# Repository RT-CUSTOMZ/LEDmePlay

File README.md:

# LEDmeplay-ESP32: Retro Arcade auf dem 32x32 RGB-Matrix-Display

Willkommen zum LEDmeplay-ESP32-Projekt!  

Dieses Projekt bringt die klassischen LEDmeplay-Spiele von Mithotronic auf ein neues Level: Mit einem leistungsstarken ESP32 als Herzstück lassen sich mehrere Arcade-Spiele auf einem 32x32 Punkte großen RGB-LED-Matrix-Display ausführen und bequem über ein Startmenü auswählen.  
Ziel ist es, ein modulares Open-Source-System zu bieten, das an das Ursprungsprojekt **LEDmeplay für Arduino Mega 2560** anknüpft, aber durch die neue Hardware umfangreicher, moderner und vielseitiger wird.

## Übersicht

- **Plattform:** ESP32
- **Display:** 32x32 RGB-Matrix-LEDs
- **Projekttyp:** PlattformIO-Projekt (Arduino-Shell)
- **Basis:** Erweiterung des Originals von Mithotronic
- **Weitere Inhalte:** FreeCAD-Dateien (Gehäuse-Design als 3D-Druck), KiCad-Schaltpläne (Elektronik), SVG (Laser-Dateien für Gehäuse)

## Hauptfeatures & Verbesserungen

- **Mehrere Spiele:** Dank ESP32 können viele Spiele im Flash gespeichert und via Startmenü ausgewählt werden.
- **Zentrale Spiele-Bibliothek:** Gemeinsame Spiel-Logik und wiederkehrende Routinen wurden als Bibliothek gekapselt – optimale Basis für eigene Spiele-Entwicklungen und unkomplizierte Erweiterbarkeit.
- **Konstante Spielgeschwindigkeit:** Trotz höherer CPU-Geschwindigkeit laufen die klassischen Spiele weiterhin in Original-Geschwindigkeit.
- **Möglichkeit für aufwendigere Spiele:** Der ESP32 eröffnet neue Potenziale für anspruchsvollere Spiele.
- **Gut dokumentierte Beispieldateien:** CAD- und Layout-Daten unterstützen beim Nachbau.

## Bekannte Einschränkungen

- **IO-Pin-Engpass:** Die verfügbaren Pins des ESP32 sind durch Display, Steuerelemente u.a. Geräte fast vollständig belegt.
- **Gestiegene Komplexität:** Das Management mehrerer Spiele sowie die Menüstrukturen erhöhen die Komplexität des Codes. Dies kann das ursprüngliche Ziel, Einsteigerinnen und Einsteigern das Programmieren beizubringen, erschweren.

## Projektstruktur

Das Repository ist logisch gegliedert – jedes Unterverzeichnis enthält klar umrissene Inhalte für die einzelnen Projektaspekte:

| Verzeichnis         | Inhalt                                                                                  |
|---------------------|----------------------------------------------------------------------------------------|
| `/src`              | Hauptquellcode für das ESP32-Board, inkl. Spiele, Menü, Bibliotheken                   |
| `/lib`              | Wiederverwendbare Bibliotheken für Spiel-Logik, Displaysteuerung usw.                  |
| `/data`             | Ressourcen wie Fonts, Sprites und Leveldaten                                           |
| `/hardware/` | FreeCAD-Dateien für alle Gehäuseteile (STL für 3D-Druck lassen sich daraus erzeugen) sowie SVG-Dateien, um Gehäuseteile (Frontplatte, Halterungen) mit dem Lasercutter zu fertigen  |
| `/hardware/KiCad/`   | KiCad-Projektdateien, Schaltpläne und Boardlayouts für die Elektronik                  |
| `/docs`             | Dokumentation, Tutorials, Installationsanleitungen                                     |

## Installation & Quickstart

1. **Voraussetzungen**
    - ESP32-Board
    - Windows, Mac oder Linux mit [PlatformIO](https://platformio.org/) und Arduino-Core
    - Lötkolben und Basiselektronik-Kenntnisse für Aufbau

2. **Firmware flashen**
    - Repository klonen:
      ```bash
      git clone https://github.com/RT-CUSTOMZ/LEDmePlay.git
      ```
    - PlatformIO-Projekt in VSCode öffnen
    - Board- und Port-Einstellungen anpassen (siehe `platformio.ini`)
    - Kompilieren & Upload:
      ```bash
      pio run --target upload
      ```

3. **Spiele auswählen**
    - Das Startmenü erscheint automatisch nach dem Boot.
    - Spiele lassen sich über angeschlossene Taster auswählen und starten.

## Hardware & Gehäuse

- **3D-Druckteile:**  
  Im Verzeichnis `/hardware/freecad` findest du alle FreeCAD-Dateien (FCStd), mit denen du die Gehäuseteile (z.B. Frontplatten, Halterungen) direkt im 3D-Drucker als STL exportieren kannst.

- **Elektronik und Platinen:**  
  Die Schaltpläne und Board-Layouts sind im Verzeichnis `/hardware/kicad` als KiCad-Projekt (Schaltplandateien, PCB) abgelegt.

- **Laser-Dateien:**  
  Vorlagen für Lasercutter (z.B. Acryl-Front, Tasten-Bohrungen) befinden sich unter `/hardware/`.

## Eigene Spiele entwickeln

- Die gemeinsame Spielelogik steht als Bibliothek unter `/lib` zur Verfügung.
- Beispielprojekte im `/src`-Verzeichnis können dupliziert und angepasst werden.

## Hinweise & Credits

- Dieses Projekt basiert auf dem genialen Ansatz von [Mithotronic LEDmeplay](https://mithotronic.de/ledmeplay.php)
- Bitte respektiere Lizenzen und Quellen beim Weiterverbreiten und Forken.
- Feedback, Fehlerberichte und Spielbeiträge gerne als Pull Request!

**Viel Spaß mit LEDmeplay-ESP32!**

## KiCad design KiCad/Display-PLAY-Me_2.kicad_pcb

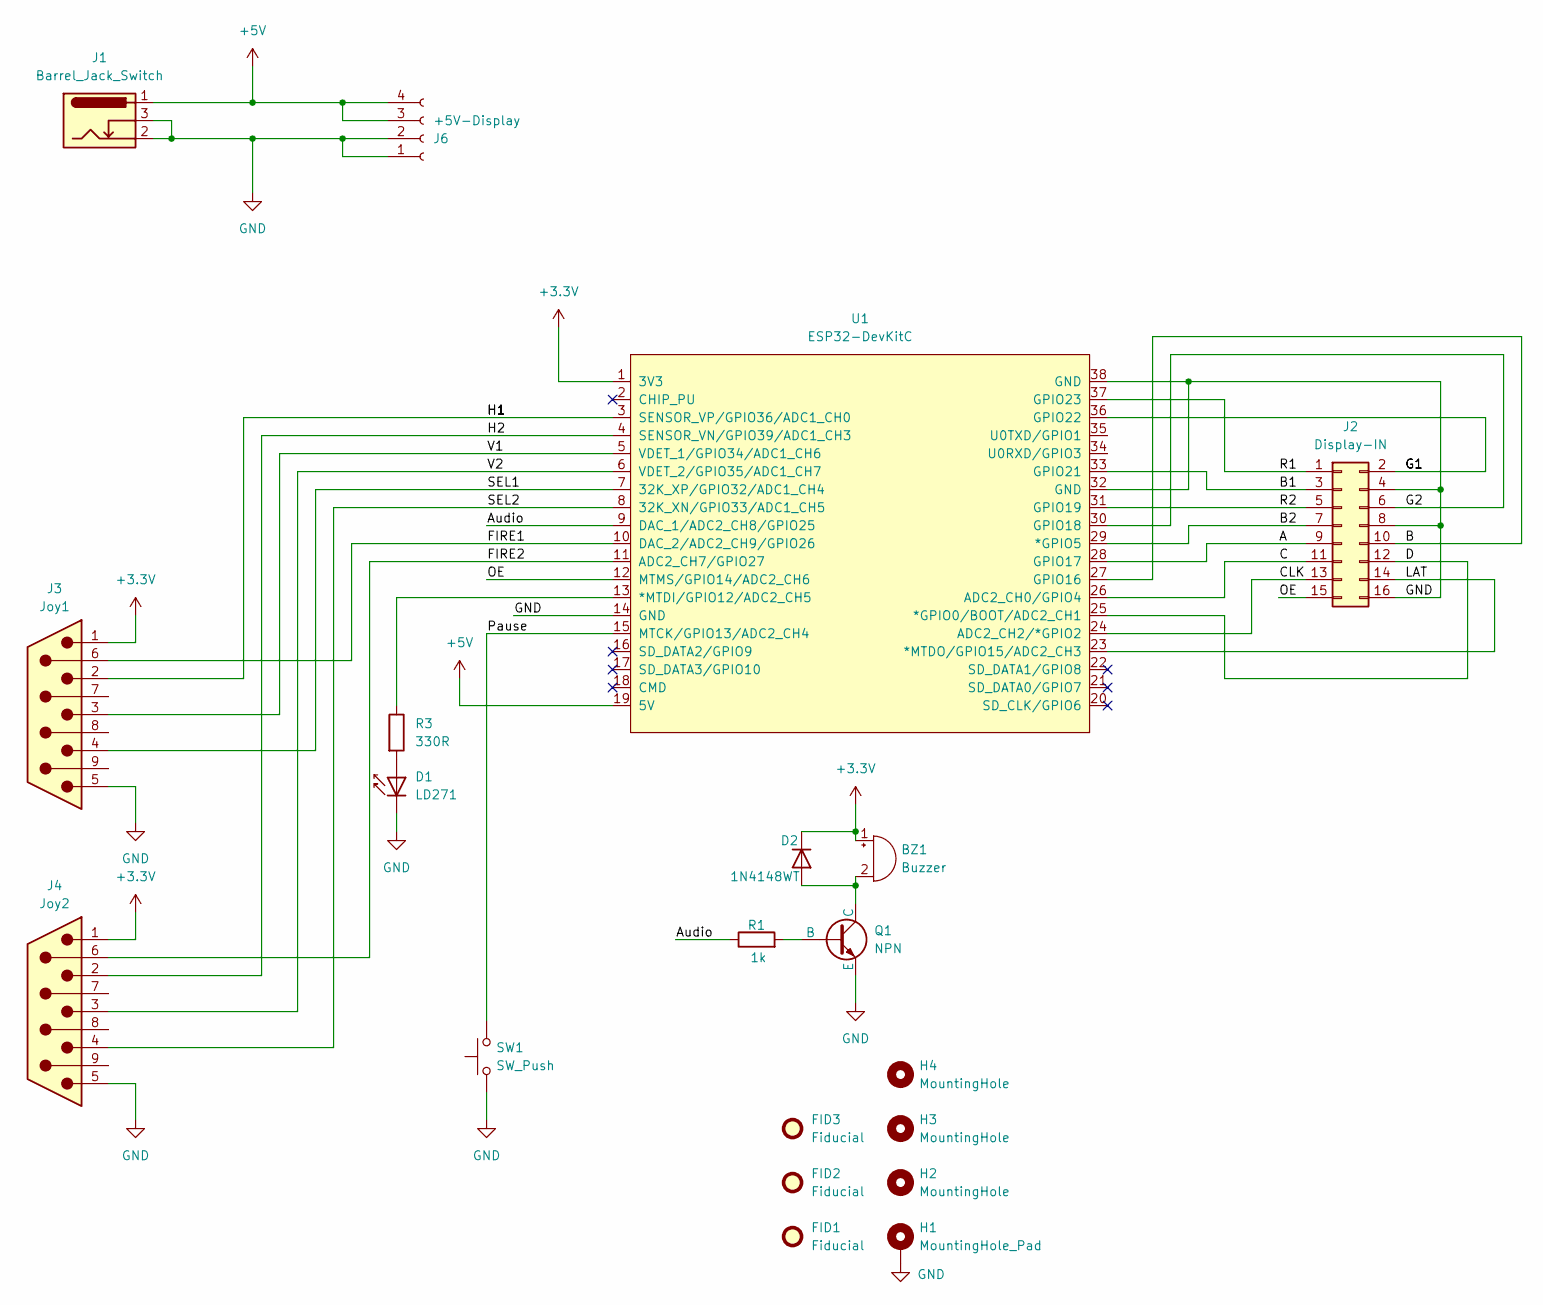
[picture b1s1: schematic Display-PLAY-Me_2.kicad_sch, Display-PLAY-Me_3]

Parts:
BZ1: Buzzer; MagneticBuzzer_PUI_AT-0927-TT-6-R
D1: LD271; LED_D5.0mm_IRGrey
D2: 1N4148WT; D_A-405_P12.70mm_Horizontal
FID1, FID2, FID3: Fiducial; Fiducial_1.5mm_Mask3mm
H1: MountingHole_Pad; MountingHole_3.5mm_Pad_TopBottom
H2, H3, H4: MountingHole; MountingHole_3.5mm
J1: Barrel_Jack_Switch; BarrelJack_Wuerth_6941xx301002
J2: Display-IN; IDC-Header_2x08_P2.54mm_Vertical
J3: Joy1; DSUB-9_Female_Horizontal_P2.77x2.84mm_EdgePinOffset4.94mm_H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
J4: Joy2; DSUB-9_Female_Horizontal_P2.77x2.84mm_EdgePinOffset4.94mm_H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
J6: +5V-Display; PhoenixContact_MSTBA_2,5_4-G-5,08_1x04_P5.08mm_Horizontal
Q1: NPN; TO-92L
R1: 1k; R_Axial_DIN0207_L6.3mm_D2.5mm_P10.16mm_Horizontal
R3: 330R; R_Axial_DIN0207_L6.3mm_D2.5mm_P10.16mm_Horizontal
SW1: SW_Push; SW_Tactile_SPST_Angled_PTS645Vx31-2LFS
U1: ESP32-DevKitC

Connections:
+3.3V: BZ1.1 (+), D2.1 (K), J3.1, J4.1, U1.1 (3V3)
+5V: J1.1, J6.3, J6.4, U1.19 (5V)
/A: J2.9, U1.28 (GPIO17)
/Audio: R1.1, U1.9 (DAC_1/ADC2_CH8/GPIO25)
/B: J2.10, U1.27 (GPIO16)
/B1: J2.3, U1.33 (GPIO21)
/B2: J2.7, U1.29 (*GPIO5)
/C: J2.11, U1.26 (ADC2_CH0/GPIO4)
/CLK: J2.13, U1.24 (ADC2_CH2/*GPIO2)
/D: J2.12, U1.25 (*GPIO0/BOOT/ADC2_CH1)
/FIRE1: J3.6, U1.10 (DAC_2/ADC2_CH9/GPIO26)
/FIRE2: J4.6, U1.11 (ADC2_CH7/GPIO27)
/G2: J2.6, U1.30 (GPIO18)
/H2: J4.2, U1.4 (SENSOR_VN/GPIO39/ADC1_CH3)
/LAT: J2.14, U1.23 (*MTDO/GPIO15/ADC2_CH3)
/OE: J2.15, U1.12 (MTMS/GPIO14/ADC2_CH6)
/Pause: SW1.2, U1.15 (MTCK/GPIO13/ADC2_CH4)
/R1: J2.1, U1.37 (GPIO23)
/R2: J2.5, U1.31 (GPIO19)
/SEL1: J3.4, U1.7 (32K_XP/GPIO32/ADC1_CH4)
/SEL2: J4.4, U1.8 (32K_XN/GPIO33/ADC1_CH5)
/V1: J3.3, U1.5 (VDET_1/GPIO34/ADC1_CH6)
/V2: J4.3, U1.6 (VDET_2/GPIO35/ADC1_CH7)
GND: D1.1 (K), H1.1, J1.2, J1.3, J2.4, J2.8, J2.16, J3.5, J4.5, J6.1, J6.2, Q1.3 (E), SW1.1, U1.14 (GND), U1.32 (GND), U1.38 (GND)
unnamed: BZ1.2 (-), D2.2 (A), Q1.1 (C)
unnamed: D1.2 (A), R3.2
unnamed: J2.2, U1.36 (GPIO22)
unnamed: Q1.2 (B), R1.2
unnamed: R3.1, U1.13 (*MTDI/GPIO12/ADC2_CH5)
unnamed: J3.2, U1.3 (SENSOR_VP/GPIO36/ADC1_CH0)

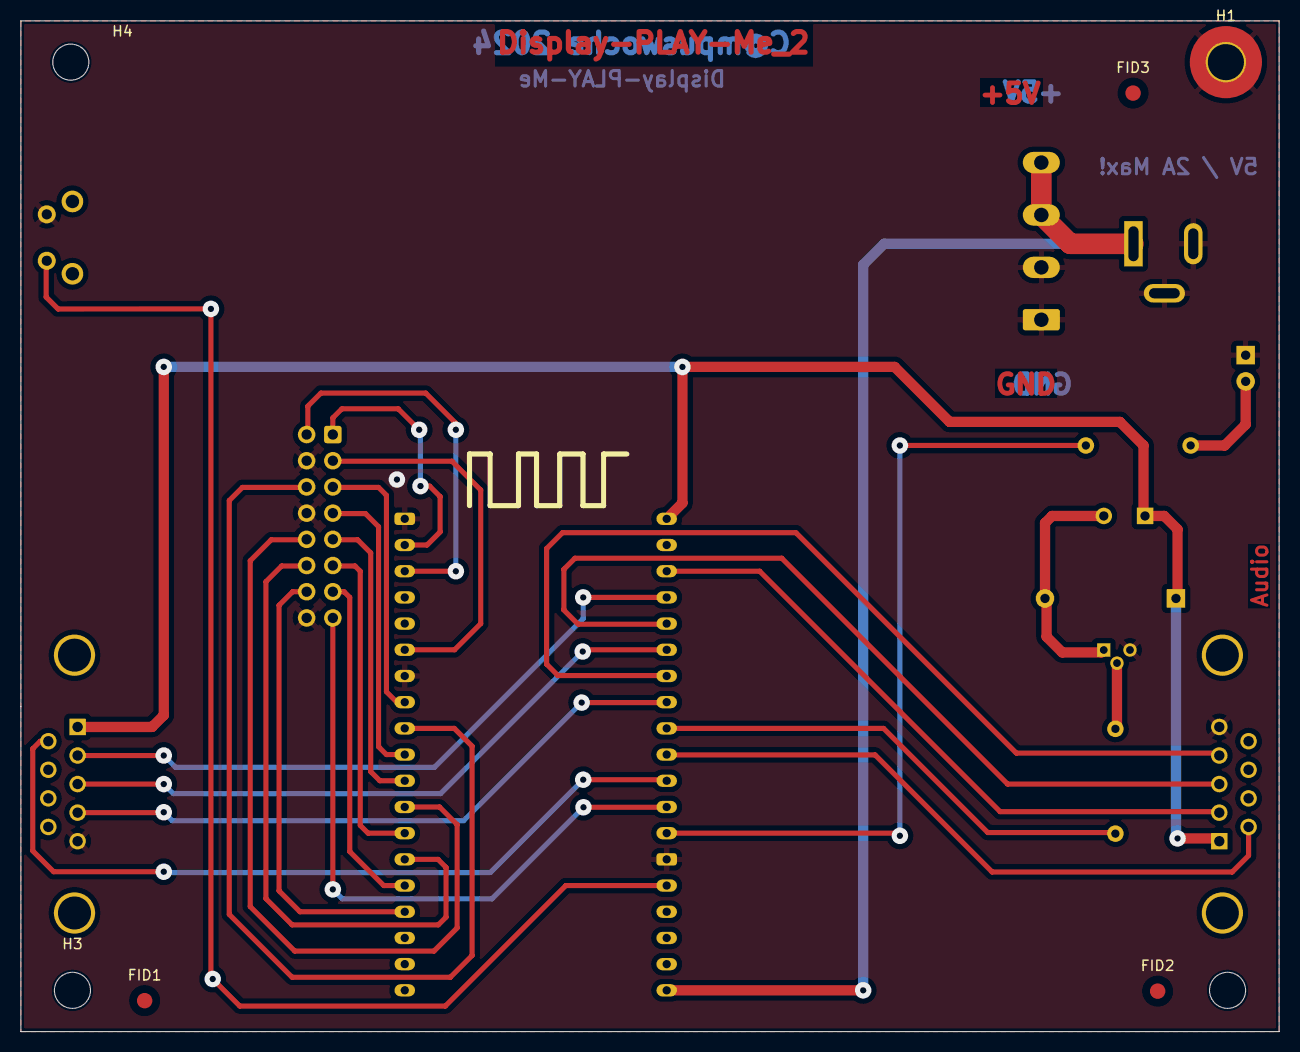
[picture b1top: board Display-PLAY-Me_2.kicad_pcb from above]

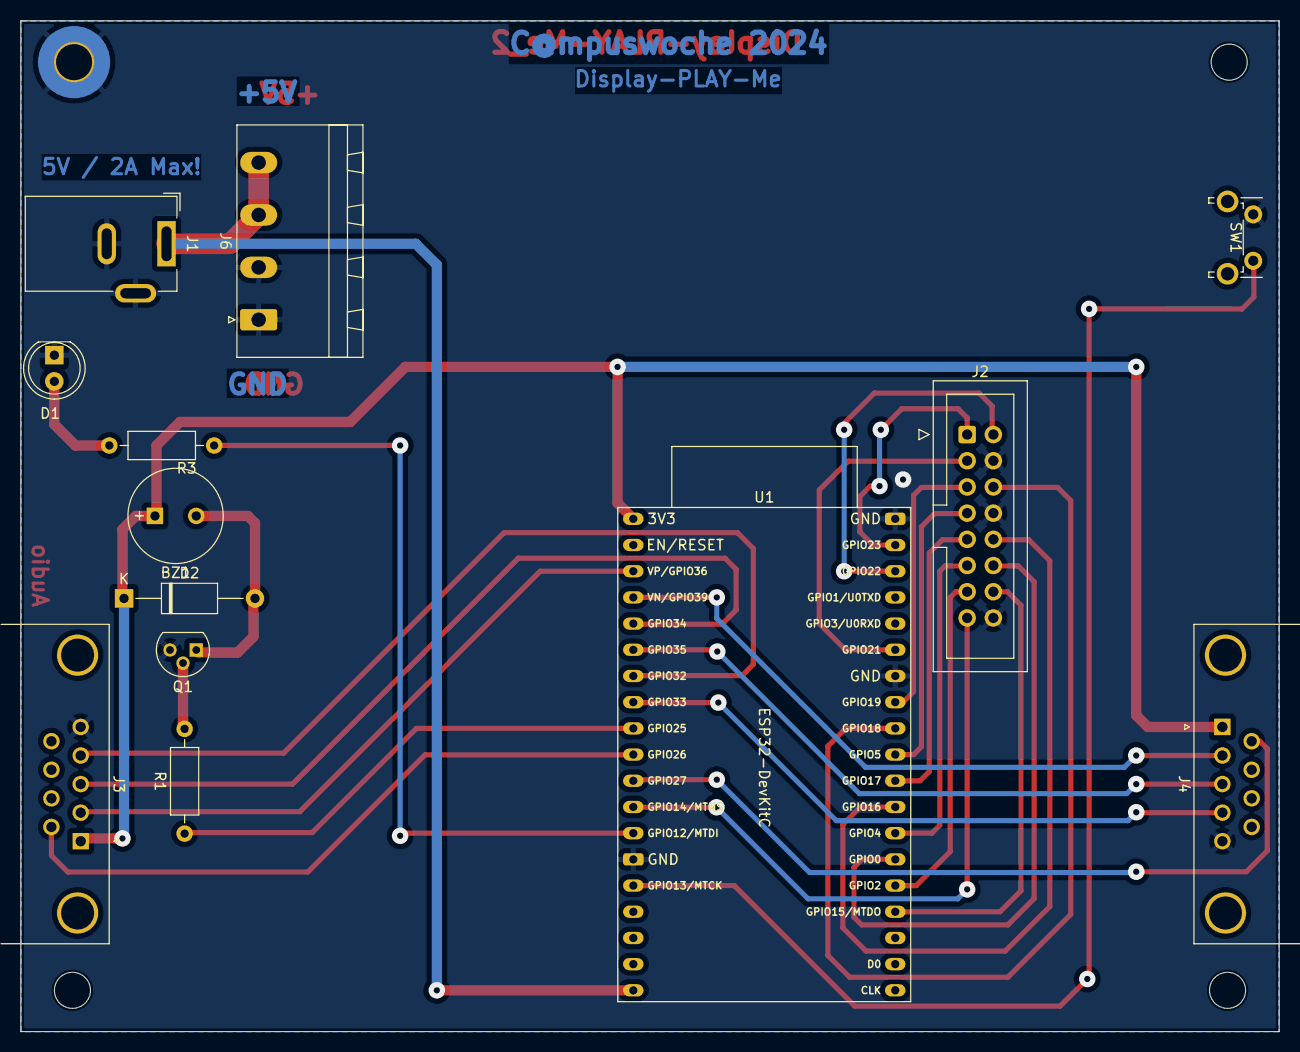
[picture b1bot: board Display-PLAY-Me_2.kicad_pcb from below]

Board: 2 copper layers, 122.0 x 98.0 mm, 20 parts (13 on the bottom side), 30 nets.

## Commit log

2025-07-25 Initialer Commit um das Projekt entlich online zu stellen.
